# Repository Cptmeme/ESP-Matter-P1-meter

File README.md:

# Matter P1 Smart-Meter Monitor

Firmware that turns the **Leotro Universal P1 Port Dongle** (ESP32-S3) into a
Matter **Electrical Sensor**. It reads the DSMR/P1 telegram from a smart meter
and publishes live power and cumulative energy over Matter (Wi-Fi or Thread).

Hardware: <https://github.com/Leotro-Engineering/Universal-P1-Port-Dongle>

## What it exposes

A single aggregate **Electrical Sensor** endpoint with:

| Matter cluster                     | Attribute / event            | Source (OBIS)                     |
|------------------------------------|------------------------------|-----------------------------------|
| Electrical Power Measurement       | `ActivePower` (net, mW)      | `1-0:1.7.0` − `1-0:2.7.0`         |
| Electrical Power Measurement       | `Voltage` (mV)               | `1-0:32.7.0` (L1)                 |
| Electrical Power Measurement       | `ActiveCurrent` (mA)         | `1-0:31.7.0` (L1)                 |
| Electrical Energy Measurement      | `CumulativeEnergyImported`   | `1-0:1.8.1` + `1-0:1.8.2`         |
| Electrical Energy Measurement      | `CumulativeEnergyExported`   | `1-0:2.8.1` + `1-0:2.8.2`         |

`ActivePower` is the net of import and export, so a house exporting solar power
reports a negative value. Both single-phase and three-phase DSMR 4/5 meters are
auto-detected; the aggregate endpoint uses the total power and the L1
voltage/current as representative values.

> Note: the Electrical Power/Energy Measurement clusters are Matter 1.3+.
> Home Assistant reads them well; Apple/Google Home support is currently limited.

## Pin configuration

Defaults match the Universal P1 Dongle and are configurable under
`idf.py menuconfig` → *P1 Dongle Configuration*:

| Function                          | GPIO   | Kconfig             |
|-----------------------------------|--------|---------------------|
| P1 data in, UART RX (from meter)  | 1      | `P1_UART_RX_GPIO`   |
| Data-request line (to meter)      | 2      | `P1_REQUEST_GPIO`   |
| P1 data out, UART TX (passthrough)| 42     | `P1_TX_GPIO`        |
| Downstream request in (TXREQ)     | 41     | `P1_TXREQ_GPIO`     |
| UART peripheral                   | 1      | `P1_UART_NUM`       |
| Baud rate                         | 115200 | `P1_UART_BAUD_RATE` |

The P1 data line is inverted/open-collector at the meter; the dongle's
transistor restores normal UART polarity, so it is read without software
inversion. The request line is held high so a DSMR 4/5 meter streams a telegram
every second. For older DSMR 2.2/3 meters set the baud rate to 9600 and disable
`P1_VERIFY_CRC`.

## P1 passthrough (second port)

Enabled by default (`P1_PASSTHROUGH`). Every telegram received from the meter is
relayed out the dongle's second P1 port (P1TX, `TX` on GPIO42), so a downstream
device — e.g. a **HomeWizard P1 meter** — plugged into that port reads the same
data the meter sent. The dongle also supplies 5 V on that port to power the
downstream device. Matter monitoring and passthrough both run off the same meter
read, so you get a Matter sensor *and* a working pass-through port at once.

By default telegrams stream continuously, which works with HomeWizard and most
readers. To forward only while the downstream device asserts its request line,
enable `P1_PASSTHROUGH_HONOR_REQUEST` (senses `TXREQ` on GPIO41). Disable
`P1_PASSTHROUGH` entirely if you don't use the second port.

Note: you connect *one meter* to the input port (P1RX) and a downstream
*consumer device* to the output port (P1TX) — not a second meter.

## Build & flash

```
idf.py set-target esp32s3
idf.py menuconfig          # optional: adjust pins / baud
idf.py build flash monitor
```

Parsed values are logged over the console (`p1_reader` tag) so you can confirm
the meter is being read before/independent of Matter commissioning. Long-press
the BOOT button to factory-reset (decommission) the device.

## Updating the firmware

### Versions

Bump all three for every release, or the device ignores the update. The build
fails if the two numbers differ.

- `PROJECT_VER` (e.g. `"1.1"`) and `PROJECT_VER_NUMBER` (e.g. `2`) in `CMakeLists.txt`
- `CONFIG_DEVICE_SOFTWARE_VERSION_NUMBER` in `sdkconfig` / `sdkconfig.defaults.esp32c6` (same number)

### Over serial

A normal `idf.py flash` still works and writes the bootloader, partition table
and app.

### Over the air (Matter OTA over Thread)

The build also produces `build/P1-Matter-ota.bin`, a Matter OTA image. Apple
Home and Google Home only update certified devices, so you serve it yourself
with the Matter SDK's host tools. Build them from the SDK with
`./scripts/build/build_examples.py --target darwin-arm64-chip-tool --target darwin-arm64-ota-provider build`.

One-time setup: in your controller (e.g. Home Assistant), open a pairing window
for the meter, then add the provider and the meter to `chip-tool`'s fabric:

```
chip-tool pairing code 2 <setup-code-from-controller>            # meter = node 2
chip-ota-provider-app -f build/P1-Matter-ota.bin --discriminator 3841 --secured-device-port 5565 &
chip-tool pairing onnetwork-long 1 20202021 3841                 # provider = node 1
chip-tool accesscontrol write acl '[{"fabricIndex": 1, "privilege": 5, "authMode": 2, "subjects": [112233], "targets": null}, {"fabricIndex": 1, "privilege": 3, "authMode": 2, "subjects": null, "targets": [{"cluster": 41, "endpoint": null, "deviceType": null}]}]' 1 0
```

Each update (with the provider running and serving the new `P1-Matter-ota.bin`):

```
chip-tool otasoftwareupdaterequestor announce-otaprovider 1 0 2 0 2 0
chip-tool basicinformation read software-version 2 0              # afterwards: the new number
```

The meter is a sleepy Thread end device, so the download is slower than on an
always-listening Thread device; expect it to take well over ten minutes. The
meter then restarts into the new version and keeps it once it has run for a
minute while attached to the network. If it doesn't get there within 5
minutes, or crashes before that, the bootloader automatically returns to the
previous version.

Rollback needs the bootloader from this build, and the bootloader can only be
written over serial. A device that has only been updated over the air still
updates fine, it just won't roll back.

## Source layout

- `main/dsmr_parser.{h,cpp}` — OBIS/CRC16 telegram parser (no hardware deps).
- `main/p1_reader.{h,cpp}` — UART + data-request line + reader task.
- `main/electrical_measurement.{h,cpp}` — Matter EPM/EEM clusters and the
  mapping from a parsed reading to attributes/events.
- `main/app_main.cpp` — node + Electrical Sensor endpoint, wiring it together.

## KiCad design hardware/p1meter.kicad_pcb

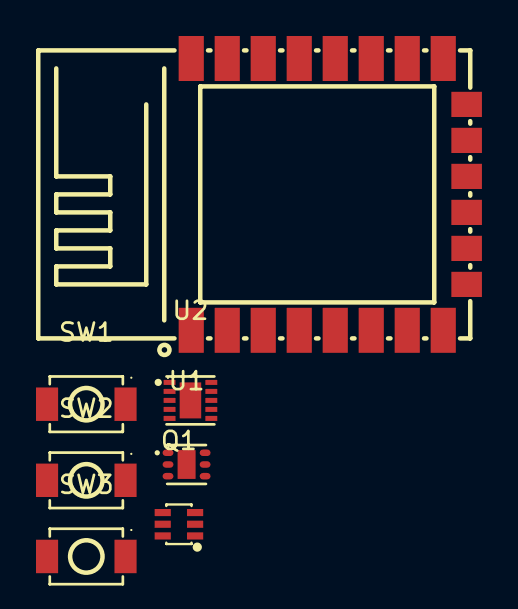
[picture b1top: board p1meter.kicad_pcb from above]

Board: 2 copper layers, 7 parts (0 on the bottom side), 6 nets, no tracks yet.

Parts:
Q1: BSS138PS,115; SOT-363_L2.0-W1.3-P0.65-LS2.1-BR
SW1: BOOT; SW-SMD_L3.9-W3.0-P4.45
SW2: RESET; SW-SMD_L3.9-W3.0-P4.45
SW3: MATTER; SW-SMD_L3.9-W3.0-P4.45
U1: TPS25200DRVR; WSON-6_L2.0-W2.0-P0.65-TL-EP
U2: TPS63900DSKR; WSON-10_L2.5-W2.5-W0.50-TL-EP
U3: WT0132C6-S5

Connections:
3.3V: U2.6 (VOUT), U3.8 (3V3)
5V LIM: U1.1 (OUT), U2.2 (SEL), U2.10 (VIN)
DATA 3V3: Q1.6 (D1), U3.13 (GPIO10)
GND: Q1.1 (S1), Q1.4 (S2), Q1.5 (G2), SW1.2, SW2.2, SW3.2, U1.5 (GND), U1.7 (EP), U2.4 (CFG2), U2.5 (CFG3), U2.8 (GND), U2.11 (EP), U3.9 (GND)
unnamed: SW1.1, U3.12 (GPIO9)
unnamed: SW3.1, U3.20 (GPIO21)
